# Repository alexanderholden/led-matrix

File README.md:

# LED matrix sign

## Key features
  - Multiplexed LED matrix
  - Adjustable brightness
  - Custom PCB and hardware design
  - WiFi enabled to allow for on-demand display changes
## System architecture
1. LED Matrix
   - LEDs arranged as an NxM grid
   - Rows and columns multiplexed reducing pin usage
  
2. Driver
   - 74HC595 attached to columns handle low side switching
   - CD4017 decade counters with transistors attached to rows handling scanning
  
3. Microcontroller
   - Generates clock signal
   - Updates frame buffer
   - Wi-Fi server

## Renders

- LED board

- Driver board

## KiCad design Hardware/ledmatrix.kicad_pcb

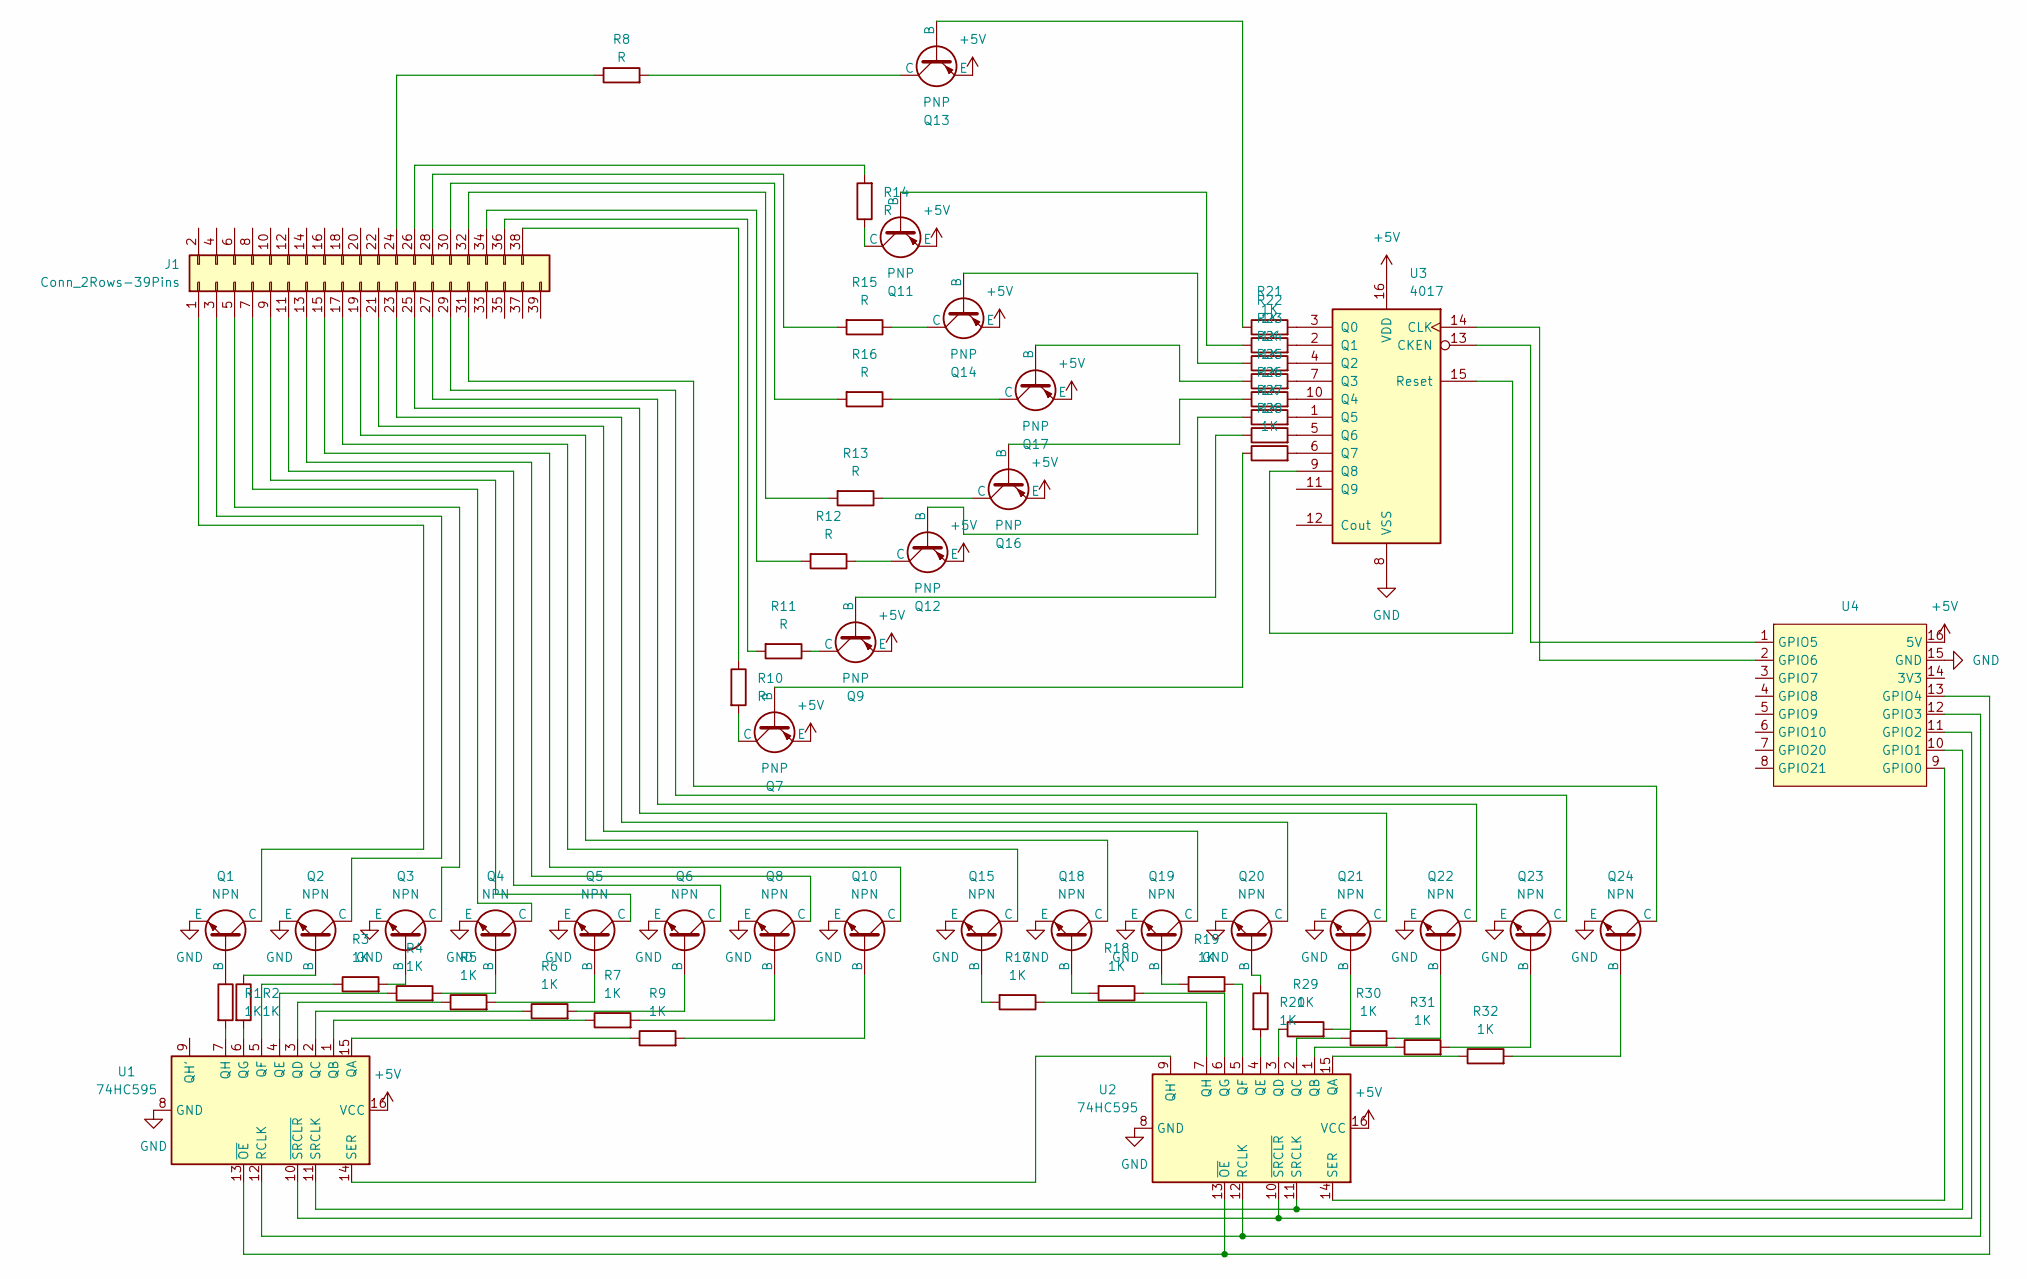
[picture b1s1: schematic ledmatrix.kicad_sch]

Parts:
J1: Conn_2Rows-39Pins; PinHeader_2x20_P2.54mm_Vertical
Q1, Q2, Q3, Q4, Q5, Q6, Q8, Q10, Q15, Q18, Q19, Q20, Q21, Q22, Q23, Q24: NPN; TO-92
Q7, Q9, Q11, Q12, Q13, Q14, Q16, Q17: PNP; TO-92
R1, R2, R3, R4, R5, R6, R7, R9, R17, R18, R19, R20, R21, R22, R23, R24, R25, R26, R27, R28, R29, R30, R31, R32: 1K; R_Axial_DIN0207_L6.3mm_D2.5mm_P10.16mm_Horizontal
R8, R10, R11, R12, R13, R14, R15, R16: R; R_Axial_DIN0207_L6.3mm_D2.5mm_P10.16mm_Horizontal
U1, U2: 74HC595; DIP-16_W7.62mm
U3: 4017; DIP-16_W7.62mm
U4: ESP32-C3-SuperMini

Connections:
+5V: Q7.3 (E), Q9.3 (E), Q11.3 (E), Q12.3 (E), Q13.3 (E), Q14.3 (E), Q16.3 (E), Q17.3 (E), U1.16 (VCC), U2.16 (VCC), U3.16 (VDD), U4.16 (5V)
GND: Q1.3 (E), Q2.3 (E), Q3.3 (E), Q4.3 (E), Q5.3 (E), Q6.3 (E), Q8.3 (E), Q10.3 (E), Q15.3 (E), Q18.3 (E), Q19.3 (E), Q20.3 (E), Q21.3 (E), Q22.3 (E), Q23.3 (E), Q24.3 (E), U1.8 (GND), U2.8 (GND), U3.8 (VSS), U4.15 (GND)
unnamed: J1.1, Q1.1 (C)
unnamed: J1.3, Q2.1 (C)
unnamed: J1.5, Q3.1 (C)
unnamed: J1.7, Q4.1 (C)
unnamed: J1.9, Q5.1 (C)
unnamed: J1.11, Q6.1 (C)
unnamed: J1.13, Q8.1 (C)
unnamed: J1.15, Q10.1 (C)
unnamed: J1.17, Q15.1 (C)
unnamed: J1.19, Q18.1 (C)
unnamed: J1.21, Q19.1 (C)
unnamed: J1.23, Q20.1 (C)
unnamed: J1.24, R8.1
unnamed: J1.25, Q21.1 (C)
unnamed: J1.26, R14.2
unnamed: J1.27, Q22.1 (C)
unnamed: J1.28, R15.2
unnamed: J1.29, Q23.1 (C)
unnamed: J1.30, R16.2
unnamed: J1.31, Q24.1 (C)
unnamed: J1.32, R13.2
unnamed: J1.34, R12.2
unnamed: J1.36, R11.2
unnamed: J1.38, R10.1
unnamed: Q1.2 (B), R1.1
unnamed: Q2.2 (B), R2.1
unnamed: Q3.2 (B), R3.2
unnamed: Q4.2 (B), R4.2
unnamed: Q5.2 (B), R5.2
unnamed: Q6.2 (B), R6.2
unnamed: Q7.2 (B), R28.1
unnamed: Q7.1 (C), R10.2
unnamed: Q8.2 (B), R7.2
unnamed: Q9.2 (B), R27.1
unnamed: Q9.1 (C), R11.1
unnamed: Q10.2 (B), R9.2
unnamed: Q11.2 (B), R22.1
unnamed: Q11.1 (C), R14.1
unnamed: Q12.2 (B), R26.1
unnamed: Q12.1 (C), R12.1
unnamed: Q13.2 (B), R21.1
unnamed: Q13.1 (C), R8.2
unnamed: Q14.2 (B), R23.1
unnamed: Q14.1 (C), R15.1
unnamed: Q15.2 (B), R17.2
unnamed: Q16.2 (B), R25.1
unnamed: Q16.1 (C), R13.1
unnamed: Q17.2 (B), R24.1
unnamed: Q17.1 (C), R16.1
unnamed: Q18.2 (B), R18.2
unnamed: Q19.2 (B), R19.2
unnamed: Q20.2 (B), R20.1
unnamed: Q21.2 (B), R29.2
unnamed: Q22.2 (B), R30.2
unnamed: Q23.2 (B), R31.2
unnamed: Q24.2 (B), R32.2
unnamed: R9.1, U1.15 (QA)
unnamed: R7.1, U1.1 (QB)
unnamed: R6.1, U1.2 (QC)
unnamed: R5.1, U1.3 (QD)
unnamed: R4.1, U1.4 (QE)
unnamed: R3.1, U1.5 (QF)
unnamed: R2.2, U1.6 (QG)
unnamed: R1.2, U1.7 (QH)
unnamed: U1.12 (RCLK), U2.12 (RCLK), U4.12 (GPIO3)
unnamed: U1.14 (SER), U2.9 (QH')
unnamed: U1.11 (SRCLK), U2.11 (SRCLK), U4.10 (GPIO1)
unnamed: U1.13 (~OE), U2.13 (~OE), U4.13 (GPIO4)
unnamed: U1.10 (~SRCLR), U2.10 (~SRCLR), U4.11 (GPIO2)
unnamed: R32.1, U2.15 (QA)
unnamed: R31.1, U2.1 (QB)
unnamed: R30.1, U2.2 (QC)
unnamed: R29.1, U2.3 (QD)
unnamed: R20.2, U2.4 (QE)
unnamed: R19.1, U2.5 (QF)
unnamed: R18.1, U2.6 (QG)
unnamed: R17.1, U2.7 (QH)
unnamed: U2.14 (SER), U4.9 (GPIO0)
unnamed: U3.13 (CKEN), U4.1 (GPIO5)
unnamed: U3.14 (CLK), U4.2 (GPIO6)
unnamed: R21.2, U3.3 (Q0)
unnamed: R22.2, U3.2 (Q1)
unnamed: R23.2, U3.4 (Q2)
unnamed: R24.2, U3.7 (Q3)
unnamed: R25.2, U3.10 (Q4)
unnamed: R26.2, U3.1 (Q5)
unnamed: R27.2, U3.5 (Q6)
unnamed: R28.2, U3.6 (Q7)
unnamed: U3.9 (Q8), U3.15 (Reset)

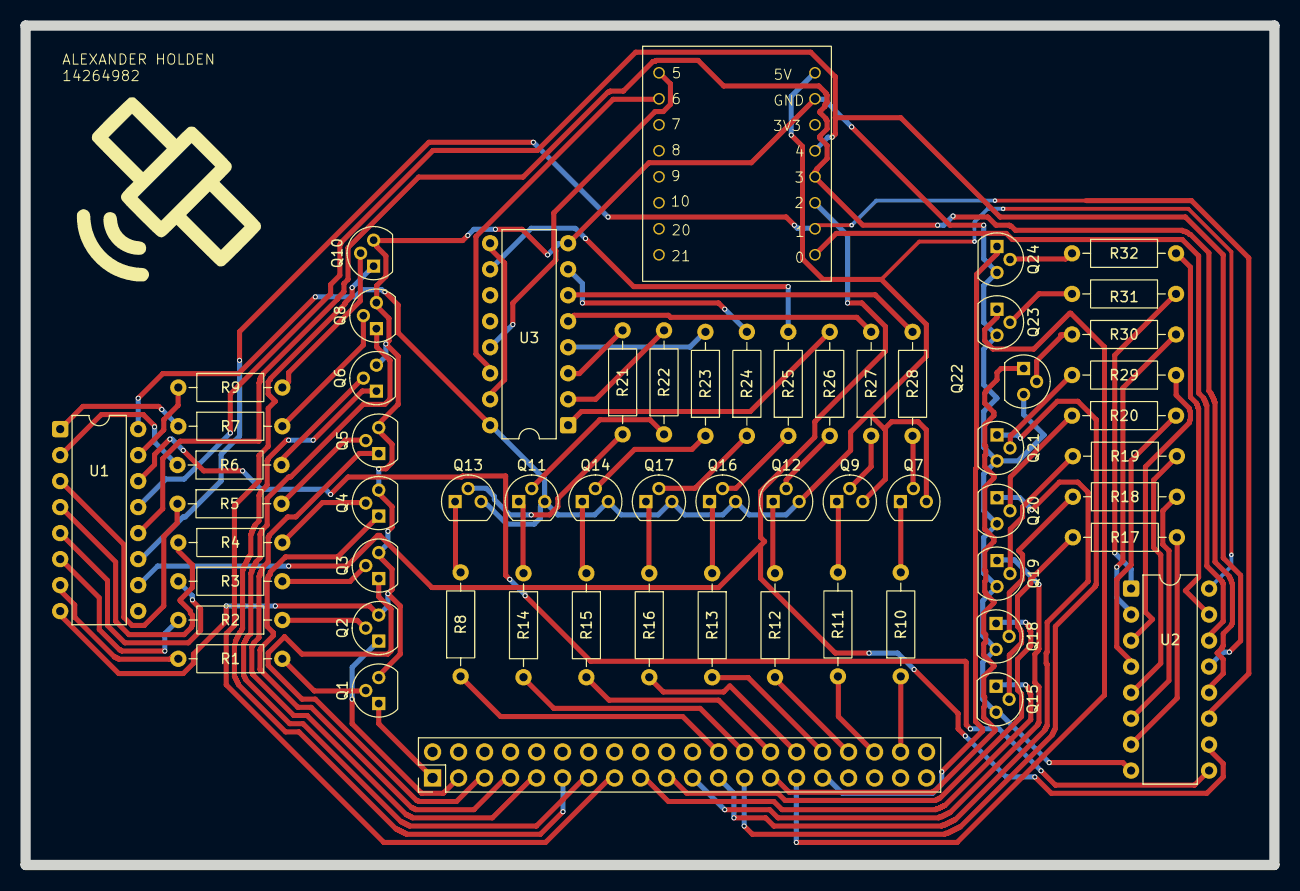
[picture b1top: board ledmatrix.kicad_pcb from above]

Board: 2 copper layers, 122.0 x 82.0 mm, 61 parts (0 on the bottom side), 91 nets.

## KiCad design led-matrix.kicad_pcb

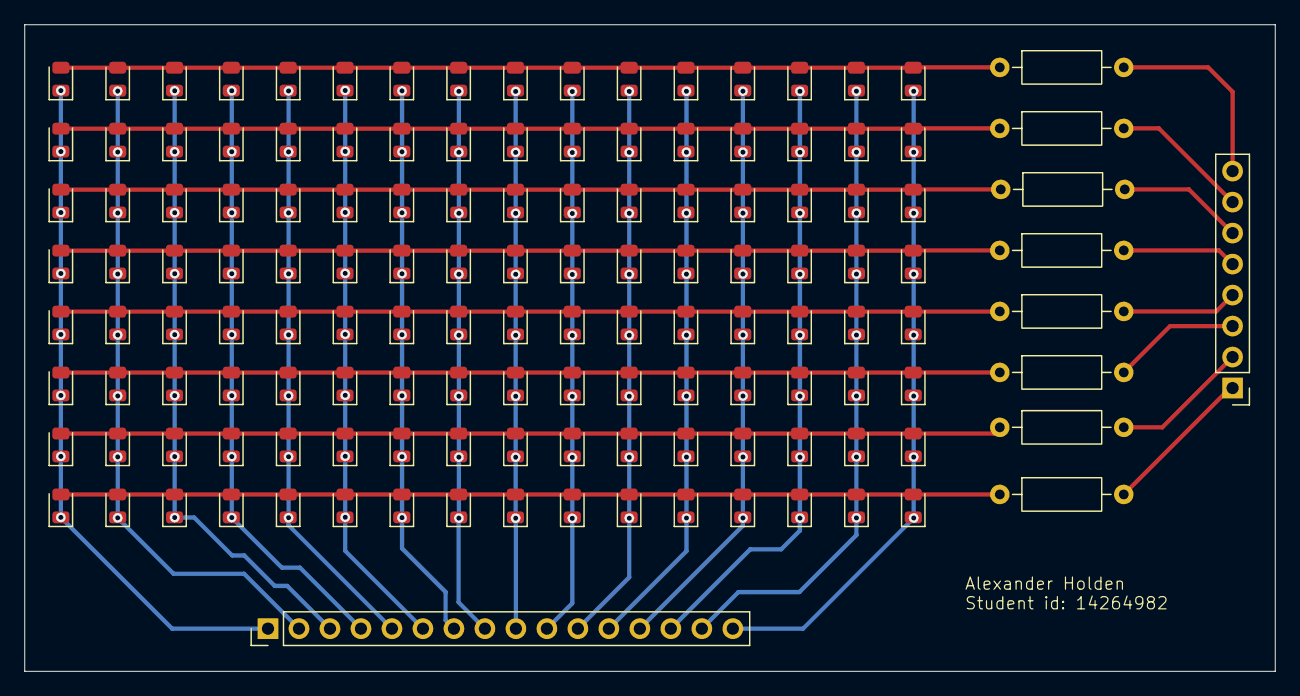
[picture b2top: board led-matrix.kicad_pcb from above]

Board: 2 copper layers, 102.5 x 53.0 mm, 138 parts (0 on the bottom side), 32 nets.

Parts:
D1, D2, D3, D4, D5, D6, D7, D8, D9, D10, D11, D12, D13, D14, D15, D16, D17, D18, D19, D20, D21, D22, D23, D24, D25, D26, D27, D28, D29, D30, D31, D32, D33, D34, D35, D36, D37, D38, D39, D40, D41, D42, D43, D44, D45, D46, D47, D48, D49, D50, D51, D52, D53, D54, D55, D56, D57, D58, D59, D60, D61, D62, D63, D64, D65, D66, D67, D68, D69, D70, D71, D72, D73, D74, D75, D76, D77, D78, D79, D80, D81, D82, D83, D84, D85, D86, D87, D88, D89, D90, D91, D92, D93, D94, D95, D96, D97, D98, D99, D100, D101, D102, D103, D104, D105, D106, D107, D108, D109, D110, D111, D112, D113, D114, D115, D116, D117, D118, D119, D120, D121, D122, D123, D124, D125, D126, D127, D128: LED; LED_0805_2012Metric_45
R1, R2, R3, R4, R5, R6, R7, R8: R; R_Axial_DIN0207_L6.3mm_D2.5mm_P10.16mm_Horizontal
U1: PinHeader_1x08_P2.54mm_Vertical
U2: PinHeader_1x16_P2.54mm_Vertical

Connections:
unnamed: D1.2 (A), D2.2 (A), D3.2 (A), D4.2 (A), D5.2 (A), D6.2 (A), D7.2 (A), D8.2 (A), D9.2 (A), D10.2 (A), D11.2 (A), D12.2 (A), D13.2 (A), D14.2 (A), D15.2 (A), D16.2 (A), R8.1
unnamed: D1.1 (K), D17.1 (K), D33.1 (K), D49.1 (K), D65.1 (K), D81.1 (K), D97.1 (K), D113.1 (K), U2.1
unnamed: D10.1 (K), D26.1 (K), D42.1 (K), D58.1 (K), D74.1 (K), D90.1 (K), D106.1 (K), D122.1 (K), U2.10
unnamed: D17.2 (A), D18.2 (A), D19.2 (A), D20.2 (A), D21.2 (A), D22.2 (A), D23.2 (A), D24.2 (A), D25.2 (A), D26.2 (A), D27.2 (A), D28.2 (A), D29.2 (A), D30.2 (A), D31.2 (A), D32.2 (A), R7.1
unnamed: D33.2 (A), D34.2 (A), D35.2 (A), D36.2 (A), D37.2 (A), D38.2 (A), D39.2 (A), D40.2 (A), D41.2 (A), D42.2 (A), D43.2 (A), D44.2 (A), D45.2 (A), D46.2 (A), D47.2 (A), D48.2 (A), R6.1
unnamed: D49.2 (A), D50.2 (A), D51.2 (A), D52.2 (A), D53.2 (A), D54.2 (A), D55.2 (A), D56.2 (A), D57.2 (A), D58.2 (A), D59.2 (A), D60.2 (A), D61.2 (A), D62.2 (A), D63.2 (A), D64.2 (A), R5.1
unnamed: D65.2 (A), D66.2 (A), D67.2 (A), D68.2 (A), D69.2 (A), D70.2 (A), D71.2 (A), D72.2 (A), D73.2 (A), D74.2 (A), D75.2 (A), D76.2 (A), D77.2 (A), D78.2 (A), D79.2 (A), D80.2 (A), R4.1
unnamed: D81.2 (A), D82.2 (A), D83.2 (A), D84.2 (A), D85.2 (A), D86.2 (A), D87.2 (A), D88.2 (A), D89.2 (A), D90.2 (A), D91.2 (A), D92.2 (A), D93.2 (A), D94.2 (A), D95.2 (A), D96.2 (A), R3.1
unnamed: D97.2 (A), D98.2 (A), D99.2 (A), D100.2 (A), D101.2 (A), D102.2 (A), D103.2 (A), D104.2 (A), D105.2 (A), D106.2 (A), D107.2 (A), D108.2 (A), D109.2 (A), D110.2 (A), D111.2 (A), D112.2 (A), R2.1
unnamed: D4.1 (K), D20.1 (K), D36.1 (K), D52.1 (K), D68.1 (K), D84.1 (K), D100.1 (K), D116.1 (K), U2.4
unnamed: D5.1 (K), D21.1 (K), D37.1 (K), D53.1 (K), D69.1 (K), D85.1 (K), D101.1 (K), D117.1 (K), U2.5
unnamed: D6.1 (K), D22.1 (K), D38.1 (K), D54.1 (K), D70.1 (K), D86.1 (K), D102.1 (K), D118.1 (K), U2.6
unnamed: D7.1 (K), D23.1 (K), D39.1 (K), D55.1 (K), D71.1 (K), D87.1 (K), D103.1 (K), D119.1 (K), U2.7
unnamed: D8.1 (K), D24.1 (K), D40.1 (K), D56.1 (K), D72.1 (K), D88.1 (K), D104.1 (K), D120.1 (K), U2.8
unnamed: D9.1 (K), D25.1 (K), D41.1 (K), D57.1 (K), D73.1 (K), D89.1 (K), D105.1 (K), D121.1 (K), U2.9
unnamed: D11.1 (K), D27.1 (K), D43.1 (K), D59.1 (K), D75.1 (K), D91.1 (K), D107.1 (K), D123.1 (K), U2.11
unnamed: D12.1 (K), D28.1 (K), D44.1 (K), D60.1 (K), D76.1 (K), D92.1 (K), D108.1 (K), D124.1 (K), U2.12
unnamed: D13.1 (K), D29.1 (K), D45.1 (K), D61.1 (K), D77.1 (K), D93.1 (K), D109.1 (K), D125.1 (K), U2.13
unnamed: D14.1 (K), D30.1 (K), D46.1 (K), D62.1 (K), D78.1 (K), D94.1 (K), D110.1 (K), D126.1 (K), U2.14
unnamed: D15.1 (K), D31.1 (K), D47.1 (K), D63.1 (K), D79.1 (K), D95.1 (K), D111.1 (K), D127.1 (K), U2.15
unnamed: D16.1 (K), D32.1 (K), D48.1 (K), D64.1 (K), D80.1 (K), D96.1 (K), D112.1 (K), D128.1 (K), U2.16
unnamed: D113.2 (A), D114.2 (A), D115.2 (A), D116.2 (A), D117.2 (A), D118.2 (A), D119.2 (A), D120.2 (A), D121.2 (A), D122.2 (A), D123.2 (A), D124.2 (A), D125.2 (A), D126.2 (A), D127.2 (A), D128.2 (A), R1.1
unnamed: D2.1 (K), D18.1 (K), D34.1 (K), D50.1 (K), D66.1 (K), D82.1 (K), D98.1 (K), D114.1 (K), U2.2
unnamed: D3.1 (K), D19.1 (K), D35.1 (K), D51.1 (K), D67.1 (K), D83.1 (K), D99.1 (K), D115.1 (K), U2.3
unnamed: R1.2, U1.1
unnamed: R2.2, U1.2
unnamed: R3.2, U1.3
unnamed: R4.2, U1.4
unnamed: R5.2, U1.5
unnamed: R6.2, U1.6
unnamed: R7.2, U1.7
unnamed: R8.2, U1.8

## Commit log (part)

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2026-02-21 test
2026-02-21 test.md removed
2026-02-21 schematic updated
2026-02-22 finished small design for testing, now sending to university pcb for fabrication
2026-02-22 added resistors to rows
2026-02-22 made slight adjustments
2026-02-23 keeping tracked
2026-02-23 pcb pics
2026-02-27 Create LICENSE
2026-03-05 clean up
